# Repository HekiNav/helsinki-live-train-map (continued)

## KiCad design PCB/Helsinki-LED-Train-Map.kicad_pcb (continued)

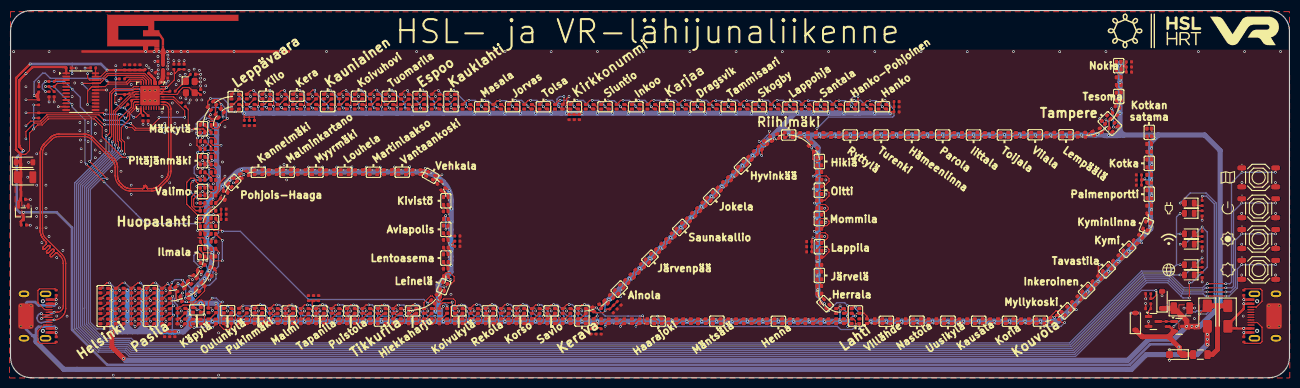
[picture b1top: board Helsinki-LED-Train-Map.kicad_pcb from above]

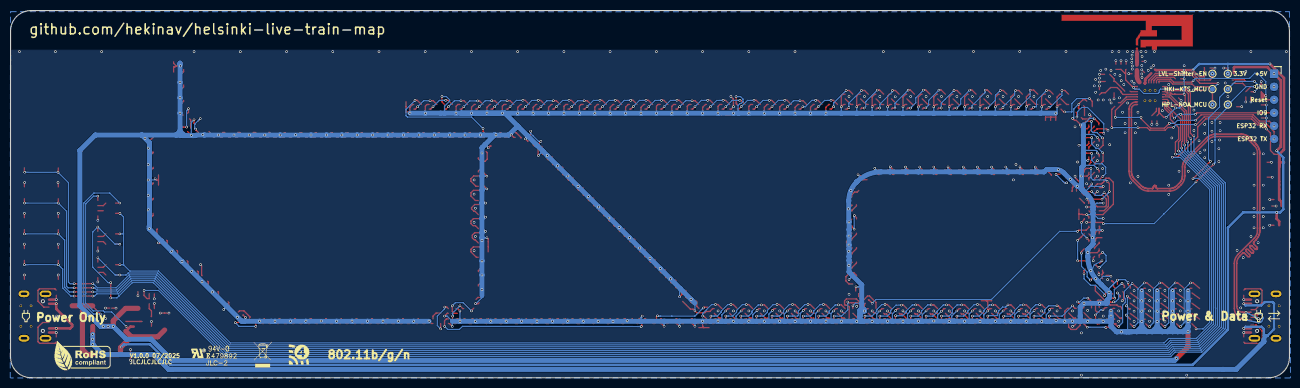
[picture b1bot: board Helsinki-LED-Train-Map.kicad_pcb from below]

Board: 2 copper layers, 249.0 x 71.5 mm, 407 parts (7 on the bottom side), 333 nets.

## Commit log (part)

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2025-07-06 pcb fixes
2025-07-07 Chris's PCB Review
2025-07-19 pcb changes
2025-07-19 readme changes
2025-07-19 readem fix
2025-08-18 Simulator added
2025-09-02 pulled code from CDFER
2025-09-05 server
2025-09-05 firmware fixes
2025-09-05 name fix
2025-09-08 blinking now happens client side
2025-09-09 moved blinking to client
2025-09-09 blinking fixes
2025-09-10 added mode system to server
2025-09-10 modes on clinet
2025-09-16 added test mode
2025-09-16 added test mode to server
2025-09-17 added cors
2025-09-19 working on simulator
2025-09-19 added comps to api and sim
2025-09-19 removed mask form on top of usb signal vias
2025-09-19 added comp to firmware
2025-09-19 web sim fix
2025-09-19 fixed sim
2025-09-19 now i actually fixed it
2025-09-19 readme changes and M train color fix
2025-09-19 wrong name of image file
2025-09-19 fixed again
2025-09-19 rotated image
2025-09-19 pcb stuff
2025-09-19 maybe the image now actually rotated
2025-09-19 image transparency
2025-09-20 added a glow effect to the sim and added new modes to api
2025-09-20 fixed shadows staying and added new modes to firmware
2025-09-21 bug fixes, sim improvemets and readme changes
2025-09-21 readme update
2025-09-21 some last minute changes
2025-09-24 fixed
2025-09-24 removed one letter
2025-12-16 readme update for new domain
2025-12-16 some old changes
2025-12-16 enabled previous blocks
2025-12-18 Rename font file in deploy workflow
2025-12-18 updated url in sim
2025-12-18 page update
2025-12-18 workflow update
2025-12-18 update workflow again
2025-12-18 path fix
2025-12-18 account id added
2025-12-18 ohh i get it now
2025-12-18 switched to https and fixed deployment file
2025-12-18 fixed prod url issue
2025-12-18 url quick fix
2025-12-19 troubleshooting
2025-12-19 added direction indication to sim and link to api
2025-12-19 web sim updates
2025-12-20 sim changes
2025-12-20 more troubleshooting :heavysob:
2025-12-20 implemented new server changes into the firmware
2025-12-20 brightness configuration
2025-12-21 sim fix
2025-12-21 added single led diffuser
2025-12-22 add diffuser
2025-12-23 tried to put a 3d model of the pcb on tje website
2025-12-24 optimized the pcb but now created heavy z-fighting
2025-12-24 still trying to figure out the 3d model
2025-12-25 some progress optimizing the model
2026-03-23 updated firmware and website
2026-03-23 zipped pcb.wrl to fit within wrangler constraints
2026-03-24 /data endpoint
2026-03-24 optimized /data to not use arduinojson
2026-03-24 readme update and website control progress
2026-03-24 working on basic config page
2026-03-24 adding more features to the control panel
2026-03-24 control panel done
2026-03-24 update readme with colors
2026-03-24 readme fix test
2026-03-24 Fix formatting in README.md for status table
2026-03-24 readme updating and color fix
2026-03-24 starting migration to typescript and drizzle
2026-03-25 ts migration
2026-03-25 got prod to finally work
2026-03-25 color fixes and readme additions
2026-03-26 db fix
2026-03-26 added demo video
2026-03-26 fixed multibetween handling
2026-03-26 opps left the debug feature there
2026-03-26 added legend to config panel and updated readme
2026-03-27 added new mode: disruptions (readme and firmware)
2026-03-27 added new mode: disruptions (server)
2026-03-27 added most delay endpoint
2026-03-27 added startup animation
2026-06-17 oops accidentally hardcoded my ip
2026-06-30 moved firmware to new repo
